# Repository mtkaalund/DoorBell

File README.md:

# DoorBell
Perhaps an over-engineered doorbell using a Arduino Pro Mini and a DFPlayer Mini.

## Hardware
The schematic are done in KiCad 5. 
A little story, at first I only meant to put a electrial schematic together, so it was easier to create a breadboard for this project.

But as I thought it would be a good pratics to create a pcb of it (mostly because it has been a long time since I did one).

As I was working with creating the schematics and the pcb, I tought it was underused, as it did'nt use all or expose the pins on the arduino or the DFPlayer Mini.
So I exposed them to the world and now it became a semi development board for the Arduino Pro Mini and DFPlayer Mini.

There are two headers "Arduino IO" and "DFPlayer IO" which expose the remaining IO's.

### DFPlayer IO
 Header Pin | DFPlayer Pin
------------|--------------
1 | DF Adkey 2
2 | DF Adkey 1
3 | DF IO 2
4 | DF IO 1
5 | DF DAC L
6 | DF DAC R

### Arduino IO
Header Pin | Arduino Pin 
-----------|-------------
1 | GND  
2 | VCC 
3 | A3   
4 | A2  
5 | A1  
6 | 13 ( SCK ) 
7 | 12 ( MISO )
8 | 9 ( Low battery LED )
9 | 8
10 | Reset
11 | 0 ( Rx )
12 | 1 ( Tx )
13 | GND
14 | VCC

### Libs
[Kicad footprints](https://github.com/joeylevy/KiCad_Arduino_Nano_DFPlayer_footprints)
[Kicad schematic symbols](https://github.com/RoboUlbricht/kicad.lib)

### Schematic
Can be found in the [hardware](https://github.com/mtkaalund/DoorBell/tree/main/hardware/DoorBell) folder as
either [Kicad Schematic](https://github.com/mtkaalund/DoorBell/blob/main/hardware/DoorBell/DoorBell.sch) or as a [PDF](https://github.com/mtkaalund/DoorBell/blob/main/hardware/DoorBell/DoorBell.pdf).

The pcb layout I have done can also be found as [Kicad PCB](https://github.com/mtkaalund/DoorBell/blob/main/hardware/DoorBell/DoorBell.kicad_pcb) or as pdf's [B_cu.pdf](https://github.com/mtkaalund/DoorBell/blob/main/hardware/DoorBell/DoorBell-B_Cu.pdf) [F_cu.pdf](https://github.com/mtkaalund/DoorBell/blob/main/hardware/DoorBell/DoorBell-F_Cu.pdf) [F_SilkS.pdf](https://github.com/mtkaalund/DoorBell/blob/main/hardware/DoorBell/DoorBell-F_SilkS.pdf)

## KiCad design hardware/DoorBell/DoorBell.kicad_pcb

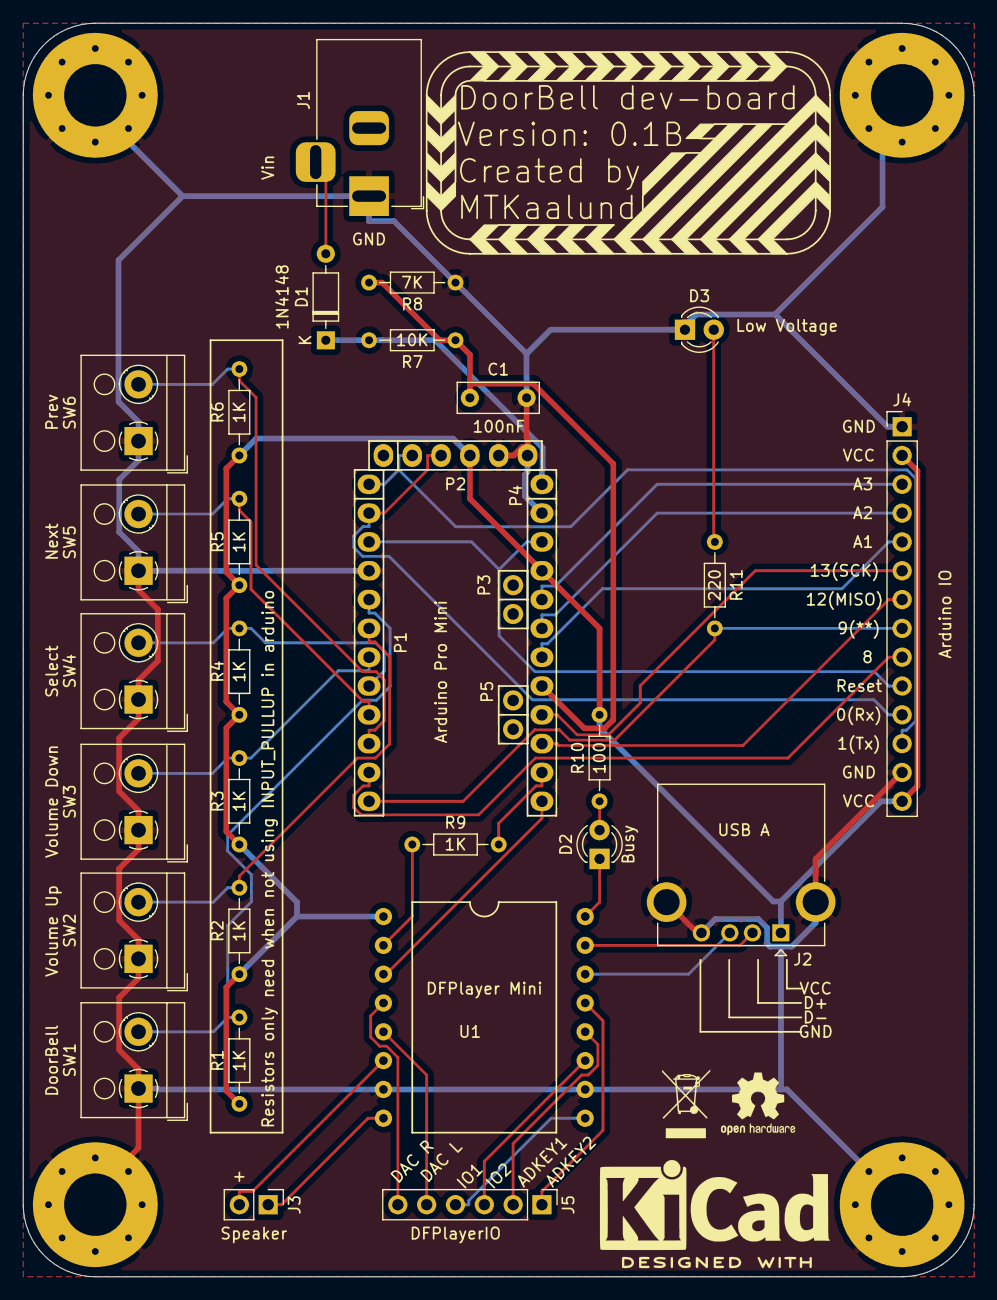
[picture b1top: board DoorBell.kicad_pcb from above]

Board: 2 copper layers, 83.8 x 110.5 mm, 39 parts (0 on the bottom side), 37 nets.

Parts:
C1: 100n; C_Rect_L7.0mm_W2.5mm_P5.00mm
D1: 1N4148; D_DO-35_SOD27_P7.62mm_Horizontal
D2: LED; LED_D3.0mm
D3: LowBatteryLED; LED_D3.0mm
H1, H2, H3, H4: MountingHole_Pad; MountingHole_5.5mm_Pad_Via
J1: Barrel_Jack_Switch_Pin3Ring; BarrelJack_Horizontal
J2: USB_A; USB_A_CONNFLY_DS1095-WNR0
J3: Speaker; PinHeader_1x02_P2.54mm_Vertical
J4: ARDUINO_IO; PinHeader_1x14_P2.54mm_Vertical
J5: DFPlayerIO; PinHeader_1x06_P2.54mm_Vertical
LOGO1: KiCad-Logo2_8mm_SilkScreen
LOGO2: WEEE-Logo_4.2x6mm_SilkScreen
LOGO3: OSHW-Logo2_7.3x6mm_SilkScreen
P1: Digital; Socket_Strip_Arduino_1x12
P2: COM; Socket_Strip_Arduino_1x06
P3, P5: ADC; Socket_Strip_Arduino_1x02
P4: Analog; Socket_Strip_Arduino_1x12
R1, R2, R3, R4, R5, R6, R9: 1K; R_Axial_DIN0204_L3.6mm_D1.6mm_P7.62mm_Horizontal
R7: 10K; R_Axial_DIN0204_L3.6mm_D1.6mm_P7.62mm_Horizontal
R8: 7K; R_Axial_DIN0204_L3.6mm_D1.6mm_P7.62mm_Horizontal
R10: 100; R_Axial_DIN0204_L3.6mm_D1.6mm_P7.62mm_Horizontal
R11: 220; R_Axial_DIN0204_L3.6mm_D1.6mm_P7.62mm_Horizontal
SW1: DoorBell; TerminalBlock_RND_205-00001_1x02_P5.00mm_Horizontal
SW2: Volume Up; TerminalBlock_RND_205-00001_1x02_P5.00mm_Horizontal
SW3: Volume Down; TerminalBlock_RND_205-00001_1x02_P5.00mm_Horizontal
SW4: Select; TerminalBlock_RND_205-00001_1x02_P5.00mm_Horizontal
SW5: Next; TerminalBlock_RND_205-00001_1x02_P5.00mm_Horizontal
SW6: Prev; TerminalBlock_RND_205-00001_1x02_P5.00mm_Horizontal
U1: DFPLAYER_MINI; DFPlayer_V2

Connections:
/0(Rx): J4.11, P1.2, P2.3
/1(Tx): J4.12, P1.1, P2.2
/8: J4.9, P1.11
/9(**): J4.8, P1.12, R11.2
/12(MISO): J4.7, P4.10
/13(SCK): J4.6, P4.9
/A1: J4.5, P4.7
/A2: J4.4, P4.6
/A3: J4.3, P4.5
/Reset: J4.10, P1.3, P4.3
DF_ADKEY_1: J5.2, U1.12
DF_ADKEY_2: J5.1, U1.13
DF_DAC_L: J5.5, U1.5
DF_DAC_R: J5.6, U1.4
DF_IO_1: J5.4, U1.9
DF_IO_2: J5.3, U1.11
DF_RX: P4.11, R9.2
DF_SPK+: J3.2, U1.6
DF_SPK-: J3.1, U1.8
DF_TX: P4.12, U1.3
GND: C1.2, D3.1, H1.1, H2.1, H3.1, H4.1, J1.1, J2.4, J2.5, J4.1, J4.13, P1.4, P2.5, P2.6, P4.2, R8.1, SW1.1, SW2.1, SW3.1, SW4.1, SW5.1, SW6.1, U1.7, U1.10
unnamed: D1.2, J1.3
unnamed: D2.1, U1.16
unnamed: D2.2, R10.1
unnamed: D3.2, R11.1
unnamed: J2.2, U1.15
unnamed: J2.3, U1.14
unnamed: R9.1, U1.2
PWR_MON: C1.1, P4.8, R7.1, R8.2
Pin2: P1.5, R1.2, SW1.2
Pin3: P1.6, R2.2, SW2.2
Pin4: P1.7, R3.2, SW3.2
Pin5: P1.8, R4.2, SW4.2
Pin6: P1.9, R5.2, SW5.2
Pin7: P1.10, R6.2, SW6.2
RAW: D1.1, P4.1, R7.2
VCC: J2.1, J4.2, J4.14, P2.4, P4.4, R1.1, R2.1, R3.1, R4.1, R5.1, R6.1, R10.2, U1.1

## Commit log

2021-01-22 first init
2021-01-23 Adding hardware schematic
2021-01-23 added .DS_Store to gitignore
2021-01-23 Finished for now the power input circuit
2021-01-23 Begun work on calculating Vraw
2021-01-23 Adding notes to pwr
2021-01-23 Updated page layout
2021-01-23 Added a hardware section to readme
2021-01-23 Almost finish with v1 of the schematic
2021-01-23 Pdf version of schematic
2021-01-23 Added hardware lib
2021-01-23 settings.json added
2021-01-23 First edition of low voltage
2021-01-24 Added mounting holes
2021-01-24 V1 of PCB finished
2021-01-24 PDF version of PCB
2021-01-24 Updated PDF of schematics
2021-01-25 Added a low voltage led to the board on pin 9.
2021-01-25 Schematic pdf updated
2021-01-25 First version of the low voltage code
2021-01-25 Updated silkscreen
2021-01-25 Added dimensions
2021-01-25 Adding adc smoothing to the code
2021-01-25 Adding table to README.md
2021-01-25 Still table
2021-01-25 Still README.md
2021-01-26 Added vscode workspace
